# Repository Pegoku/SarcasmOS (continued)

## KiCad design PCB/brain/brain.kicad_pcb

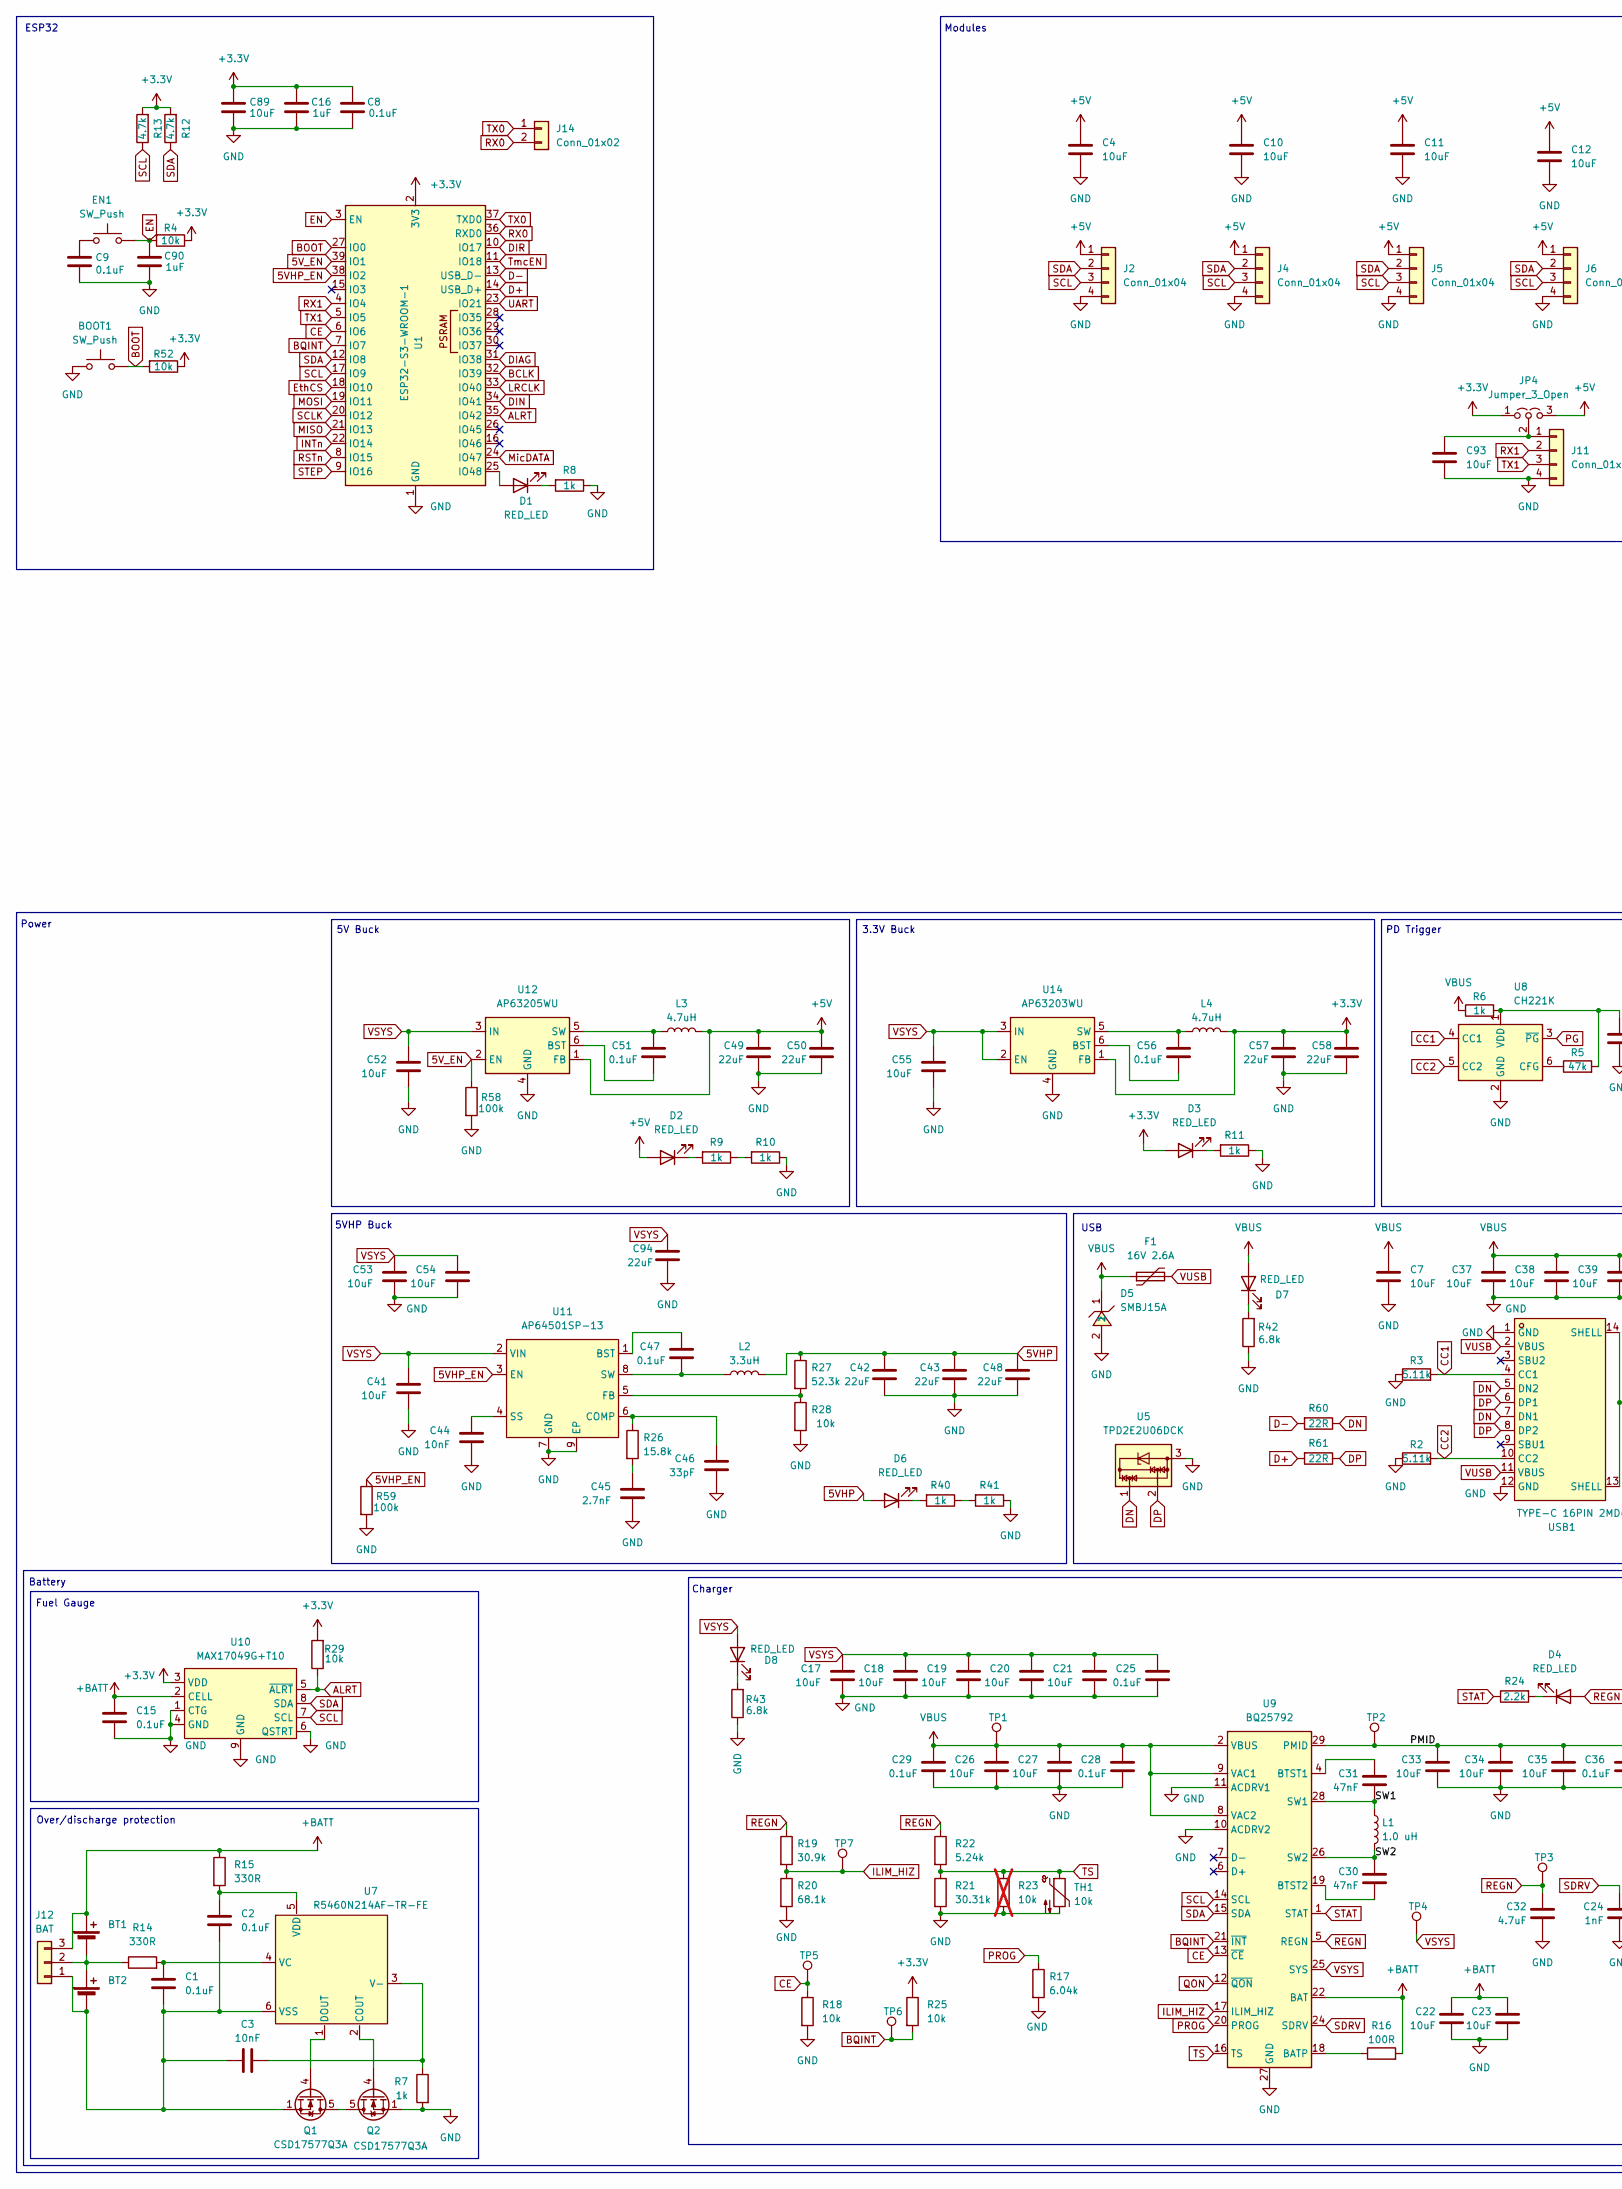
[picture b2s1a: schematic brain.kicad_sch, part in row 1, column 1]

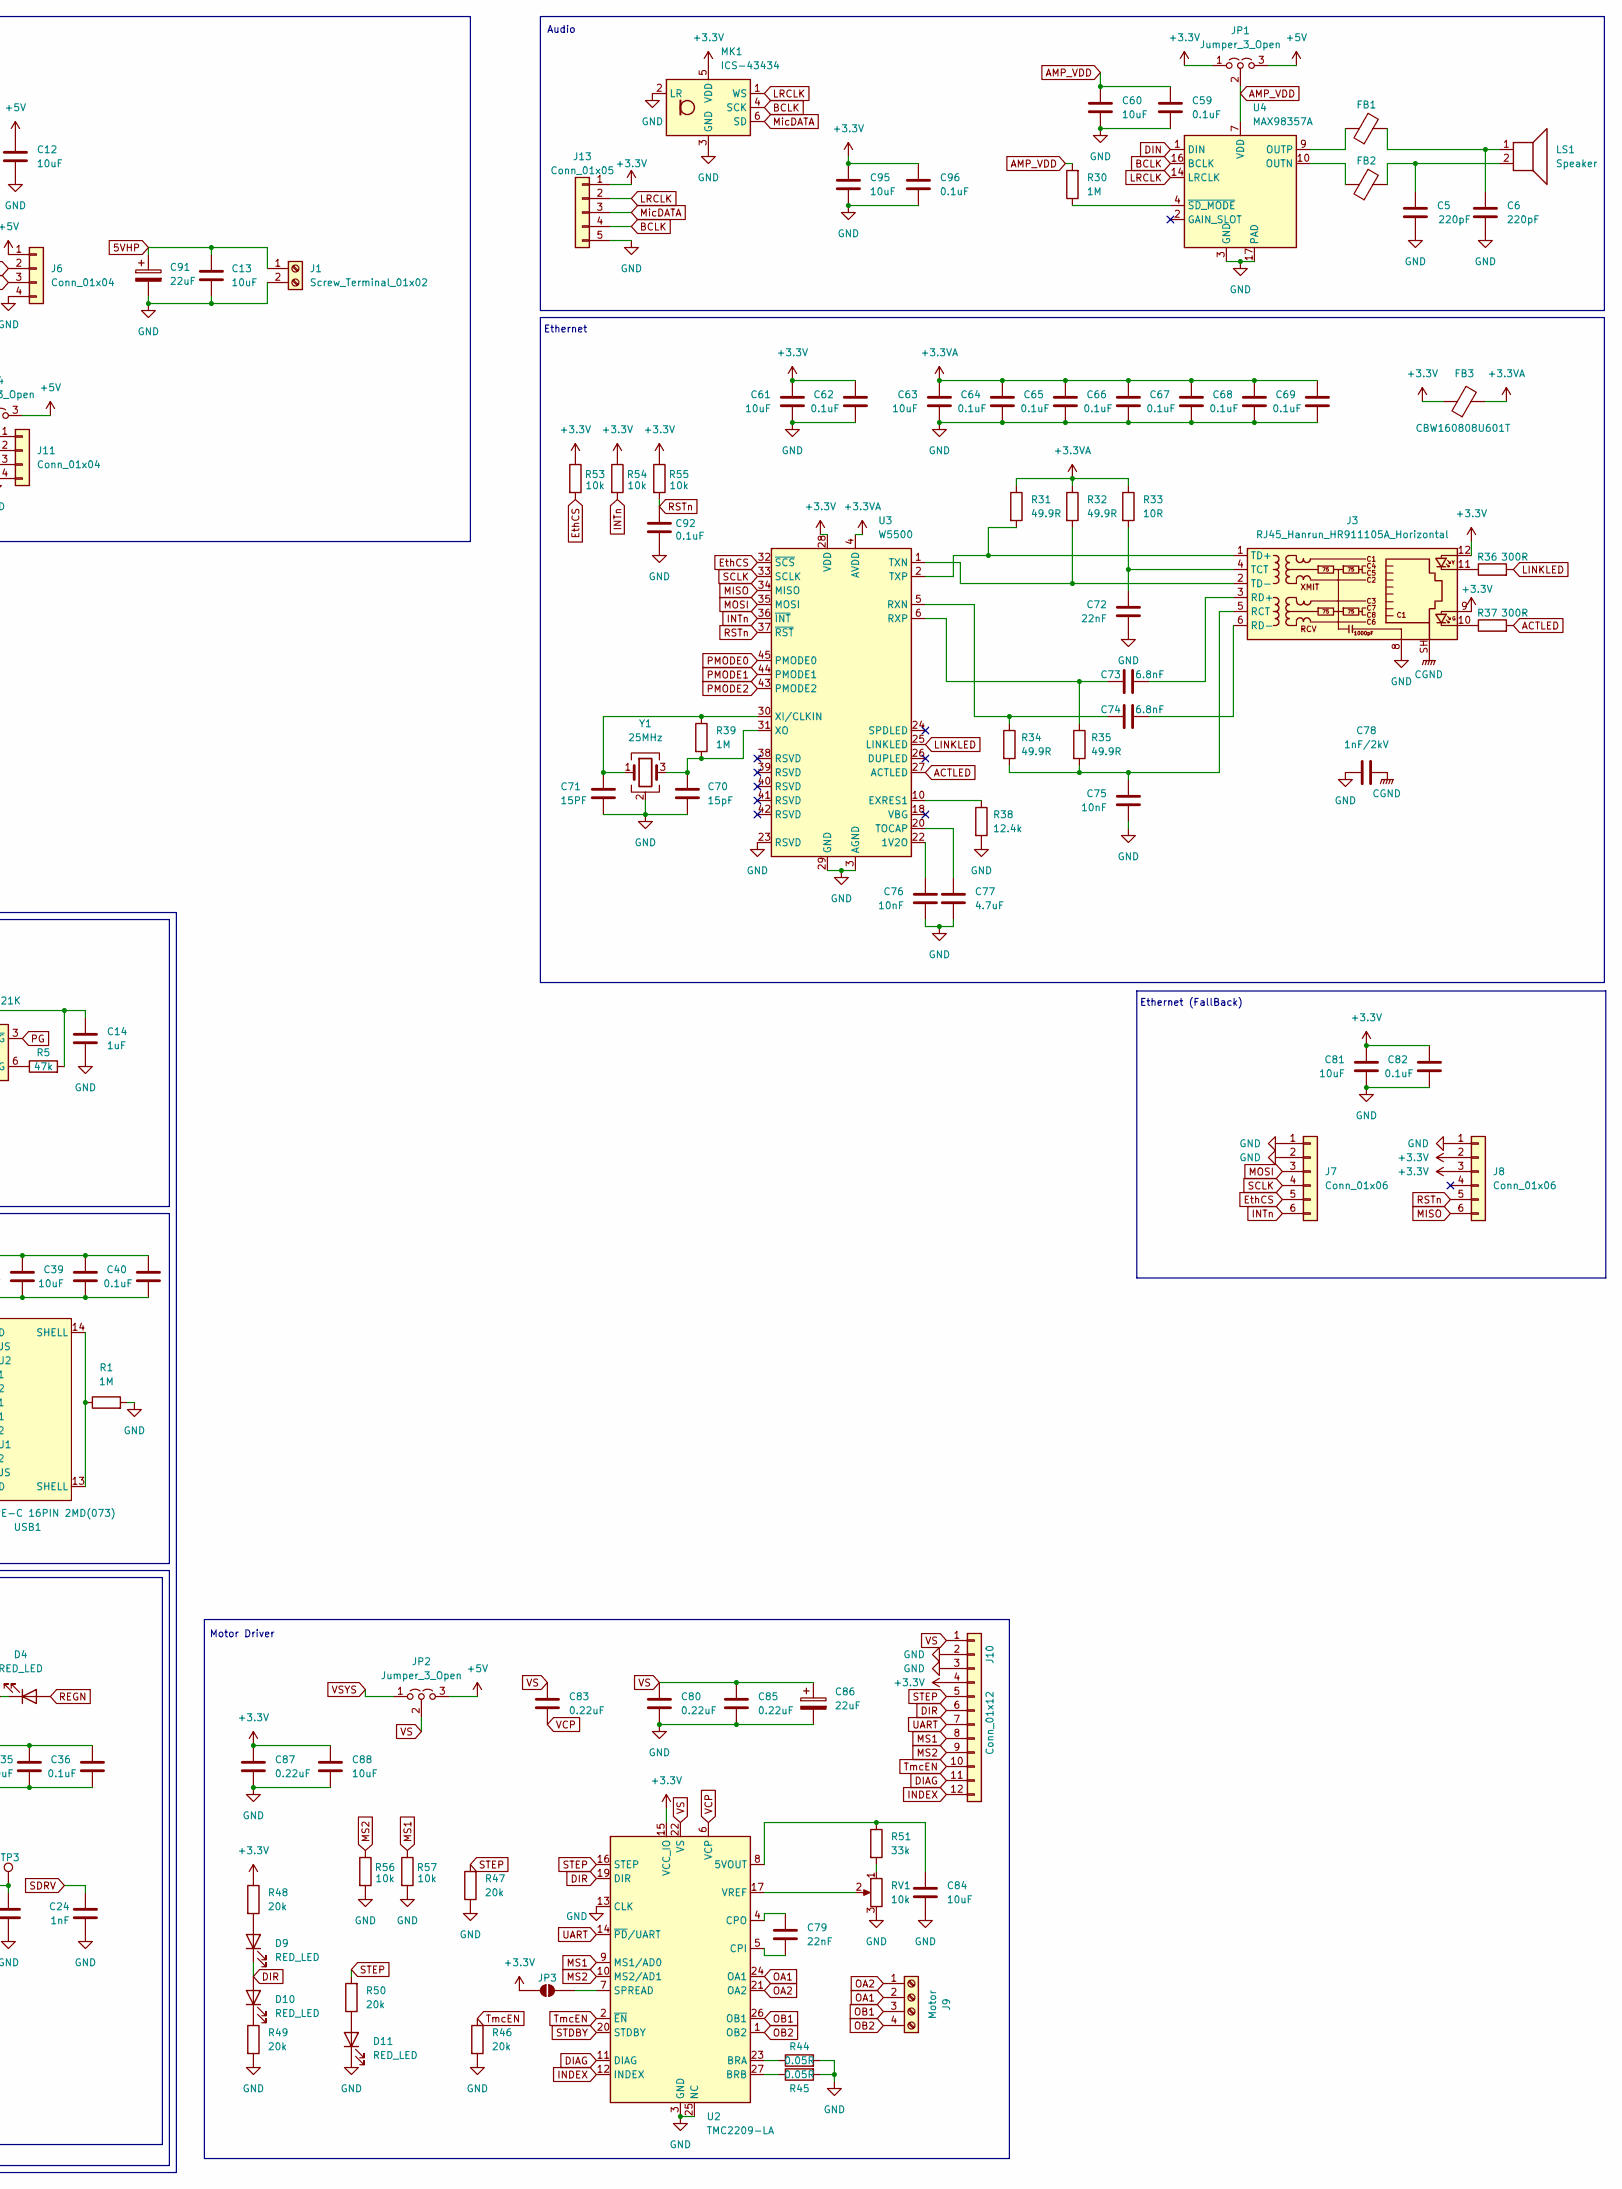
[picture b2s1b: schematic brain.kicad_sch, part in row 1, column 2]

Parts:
BOOT1: SW_Push; SW_SPST_TS-1088-xR025; LCSC Part C720477
BT1, BT2: Battery_Cell; PinHeader_1x02_P2.54mm_Vertical
C1, C2, C15, C29, C47, C51, C56, C92: 0.1uF; C_0603_1608Metric
C3, C44, C75, C76: 10nF; C_0603_1608Metric
C4, C7, C10, C11, C12, C13, C60, C61, C63, C81, C84, C88, C89, C93, C95: 10uF; C_0603_1608Metric
C5, C6: 220pF; C_0603_1608Metric
C8, C25, C28, C36, C40, C59, C62, C64, C65, C66, C67, C68, C69, C96: 0.1uF; C_0402_1005Metric; LCSC Part C77020
C9, C82: 0.1uF; C_0402_1005Metric
C14, C16, C90: 1uF; C_0603_1608Metric
C17, C18, C19, C20, C21, C22, C23, C26, C27, C33, C34, C35, C37, C38, C39, C41, C52, C53, C54, C55: 10uF; C_0603_1608Metric; LCSC Part C194427
C24: 1nF; C_0603_1608Metric
C30, C31: 47nF; C_0603_1608Metric
C32, C77: 4.7uF; C_0603_1608Metric
C42, C94: 22uF; C_0805_2012Metric; LCSC Part C162295
C43, C48, C49, C50, C57, C58: 22uF; C_0805_2012Metric
C45: 2.7nF; C_0603_1608Metric
C46: 33pF; C_0603_1608Metric
C70: 15pF; C_0603_1608Metric; LCSC Part C1644
C71: 15PF; C_0603_1608Metric; LCSC Part C1644
C72, C79: 22nF; C_0603_1608Metric
C73, C74: 6.8nF; C_0603_1608Metric
C78: 1nF/2kV; C_1206_3216Metric; LCSC Part C23631
C80, C83, C85, C87: 0.22uF; C_0603_1608Metric
C86, C91: 22uF; CAP-SMD_BD6.3-L6.6-W6.6-FD; LCSC Part C72505
D1, D2, D3, D4, D6, D7, D8, D9, D10, D11: RED_LED; LED_0603_1608Metric; LCSC Part C19171390
D5: SMBJ15A; SMB_L4.6-W3.6-LS5.3-RD; MPN SMBJ15A; LCSC Part C83846
EN1: SW_Push; SW_SPST_TS-1088-xR025; LCSC Part C720477
F1: 16V 2.6A; Fuse_1812_4532Metric_Pad1.30x3.40mm_HandSolder; LCSC Part C438899
FB1, FB2: FerriteBead; L_0603_1608Metric; LCSC Part C88989
FB3: CBW160808U601T; L_0603_1608Metric; LCSC Part C139183
J1: Screw_Terminal_01x02; TerminalBlock_Phoenix_PT-1,5-2-5.0-H_1x02_P5.00mm_Horizontal; LCSC Part C474881
J2, J4, J5, J6, J11: Conn_01x04; JST_XH_B4B-XH-A_1x04_P2.50mm_Vertical; LCSC Part C144395
J3: RJ45_Hanrun_HR911105A_Horizontal; LCSC Part C12074
J7, J8: Conn_01x06; PinSocket_1x06_P2.54mm_Vertical
J9: Motor; CONN-TH_4P-P2.54_MX128-2.54-GN01-04P-CU-Y-A; LCSC Part C5188444
J10: Conn_01x12; PinHeader_2x06_P2.54mm_Vertical
J12: BAT; JST_XH_B3B-XH-A_1x03_P2.50mm_Vertical
J13: Conn_01x05; JST_XH_B5B-XH-A_1x05_P2.50mm_Vertical
J14: Conn_01x02; PinSocket_1x02_P2.54mm_Vertical
JP1, JP2, JP4: Jumper_3_Open; PinHeader_1x03_P2.54mm_Vertical
JP3: SolderJumper_2_Open; SolderJumper-2_P1.3mm_Open_TrianglePad1.0x1.5mm
L1: 1.0 uH; IND-SMD_L7.1-W6.5-P5.60; LCSC Part C87572
L2: 3.3uH; IND-SMD_L11.5-W10.0_SMMS1040; LCSC Part C149592
L3, L4: 4.7uH; IND-SMD_L5.0-W5.0; LCSC Part C354606
LS1: Speaker; JST_XH_B2B-XH-AM_1x02_P2.50mm_Vertical
MK1: ICS-43434; InvenSense_ICS-43434-6_3.5x2.65mm
Q1, Q2: CSD17577Q3A; VSON-8_3.3x3.3mm_P0.65mm_NexFET
R1, R30, R39: 1M; R_0603_1608Metric
R2, R3: 5.11k; R_0603_1608Metric
R4, R18, R25, R28, R29, R52, R53, R54, R55, R56, R57: 10k; R_0603_1608Metric
R5: 47k; R_0603_1608Metric
R6, R7, R8, R9, R10, R11, R40, R41: 1k; R_0603_1608Metric
R12, R13: 4.7k; R_0603_1608Metric
R14, R15: 330R; R_0603_1608Metric
R16: 100R; R_0603_1608Metric
R17: 6.04k; R_0603_1608Metric
R19: 30.9k; R_0603_1608Metric
R20: 68.1k; R_0603_1608Metric
R21: 30.31k; R_0603_1608Metric
R22: 5.24k; R_0603_1608Metric
R23: 10k; R_0603_1608Metric; not fitted
R24: 2.2k; R_0603_1608Metric
R26: 15.8k; R_0603_1608Metric
R27: 52.3k; R_0603_1608Metric
R31, R32, R34, R35: 49.9R; R_0603_1608Metric
R33: 10R; R_0603_1608Metric
R36, R37: 300R; R_0603_1608Metric
R38: 12.4k; R_0603_1608Metric
R42, R43: 6.8k; R_0603_1608Metric
R44, R45: 0.05R; R_1206_3216Metric
R46, R47, R48, R49, R50: 20k; R_0603_1608Metric
R51: 33k; R_0603_1608Metric
R58, R59: 100k; R_0603_1608Metric
R60, R61: 22R; C_0402_1005Metric
RV1: 10k; RES-ADJ-SMD_3P-L3.8-W3.7_VGF39NCHXT; LCSC Part C22461454
TH1: 10k; PinHeader_1x02_P2.54mm_Vertical
TP1, TP2, TP3, TP4, TP5, TP6, TP7: TestPoint; TestPoint_Pad_D1.5mm
U1: ESP32-S3-WROOM-1; ESP32-S3-WROOM-1U; LCSC Part C2913199
U2: TMC2209-LA; VQFN-28-1EP_5x5mm_P0.5mm_EP3.7x3.7mm_ThermalVias
U3: W5500; LQFP-48_7x7mm_P0.5mm; LCSC Part C32843
U4: MAX98357A; TQFN-16-1EP_3x3mm_P0.5mm_EP1.23x1.23mm
U5: TPD2E2U06DCK; SOT-323_SC-70
U7: R5460N214AF-TR-FE; SOT-23-6_L2.9-W1.6-P0.95-LS2.8-BL; MPN R5460N214AF-TR-FE; LCSC Part C259719
U8: CH221K; SOT-23-6
U9: BQ25792; Texas_RQM0029A_VQFN-29_4x4mm_P0.4mm
U10: MAX17049G+T10; WSON-8_L2.0-W2.0-P0.50-BL-EP0.9; MPN MAX17049G+T10; LCSC Part C18185545
U11: AP64501SP-13; SOIC-8-1EP_3.9x4.9mm_P1.27mm_EP2.29x3mm_ThermalVias; MPN AP64501SP-13; LCSC Part C2071517
U12: AP63205WU; TSOT-23-6
U14: AP63203WU; TSOT-23-6
USB1: TYPE-C 16PIN 2MD(073); USB-C-SMD_TYPE-C-6PIN-2MD-073; LCSC Part C2765186
Y1: 25MHz; Crystal_SMD_3225-4Pin_3.2x2.5mm; LCSC Part C13740

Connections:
5VHP: C13.2, C42.2, C43.2, C48.2, C91.1, D6.2 (A), J1.1, L2.2, R27.1
5VHP_EN: R59.1, U1.38 (IO2), U11.3 (EN)
5V_EN: R58.1, U1.39 (IO1), U12.2 (EN)
+3.3V: C8.2, C16.2, C57.2, C58.2, C61.2, C62.2, C81.2, C82.2, C87.1, C88.2, C89.2, C95.1, C96.1, D3.2 (A), FB3.1, J3.9, J3.12, J8.2, J8.3, J10.4, J13.1, JP1.1 (A), JP3.1 (A), JP4.1 (A), L4.2, MK1.5 (VDD), R4.1, R12.2, R13.2, R25.1, R29.2, R48.1, R52.1, R53.1, R54.1, R55.1, U1.2 (3V3), U2.15 (VCC_IO), U3.28 (VDD), U10.3 (VDD), U14.1 (FB)
+3.3VA: C63.2, C64.2, C65.2, C66.2, C67.2, C68.2, C69.2, FB3.2, R31.1, R32.1, R33.1, U3.4 (AVDD), U3.8 (AVDD), U3.11 (AVDD), U3.15 (AVDD), U3.17 (AVDD), U3.21 (AVDD)
+5V: C4.2, C10.2, C11.2, C12.2, C49.2, C50.2, D2.2 (A), J2.1, J4.1, J5.1, J6.1, JP1.3 (B), JP2.3 (B), JP4.3 (B), L3.2, U12.1 (FB)
+BATT: BT1.1 (+), C15.1, C22.2, C23.2, J12.3, R15.1, R16.2, U9.22 (BAT), U9.23 (BAT), U10.2 (CELL)
/PMID: C33.2, C34.2, C35.2, C36.2, TP2.1 (1_1), U9.29 (PMID)
/SW1: C31.1, L1.1, U9.28 (SW1)
/SW2: C30.2, L1.2, U9.26 (SW2)
ACTLED: R37.2, U3.27 (ACTLED)
ALRT: R29.1, U1.35 (IO42), U10.5 (~ALRT)
AMP_VDD: C59.1, C60.1, JP1.2 (C), R30.2, U4.7 (VDD), U4.8 (VDD)
BCLK: J13.4, MK1.4 (SCK), U1.32 (IO39), U4.16 (BCLK)
BOOT: BOOT1.2, R52.2, U1.27 (IO0)
BQINT: R25.2, TP6.1 (1_1), U1.7 (IO7), U9.21 (~INT)
CC1: R3.2, U8.4 (CC1), USB1.4 (CC1)
CC2: R2.2, U8.5 (CC2), USB1.10 (CC2)
CE: R18.1, TP5.1 (1_1), U1.6 (IO6), U9.13 (~CE)
CGND: C78.2, J3.SH
D+: R61.2, U1.14 (USB_D+)
D-: R60.2, U1.13 (USB_D-)
DIAG: J10.11, U1.31 (IO38), U2.11 (DIAG)
DIN: U1.34 (IO41), U4.1 (DIN)
DIR: D9.1 (K), D10.2 (A), J10.6, U1.10 (IO17), U2.19 (DIR)
DN: R60.1, U5.1, USB1.5 (DN2), USB1.7 (DN1)
DP: R61.1, U5.2, USB1.6 (DP1), USB1.8 (DP2)
EN: C90.2, EN1.2, R4.2, U1.3 (EN)
EthCS: J7.5, R53.2, U1.18 (IO10), U3.32 (~SCS)
GND: BOOT1.1, C4.1, C5.2, C6.2, C7.1, C8.1, C9.1, C10.1, C11.1, C12.1, C13.1, C14.1, C15.2, C16.1, C17.1, C18.1, C19.1, C20.1, C21.1, C22.1, C23.1, C24.1, C25.1, C26.1, C27.1, C28.1, C29.1, C32.1, C33.1, C34.1, C35.1, C36.1, C37.1, C38.1, C39.1, C40.1, C41.1, C42.1, C43.1, C44.1, C45.1, C46.1, C48.1, C49.1, C50.1, C52.1, C53.1, C54.1, C55.1, C57.1, C58.1, C59.2, C60.2, C61.1, C62.1, C63.1, C64.1, C65.1, C66.1, C67.1, C68.1, C69.1, C70.2, C71.2, C72.1, C75.1, C76.1, C77.1, C78.1, C80.2, C81.1, C82.1, C84.1, C85.2, C86.2, C87.2, C88.1, C89.1, C90.1, C91.2, C92.1, C93.1, C94.1, C95.2, C96.2, D5.2, D11.1 (K), J1.2, J2.4, J3.8, J4.4, J5.4, J6.4, J7.1, J7.2, J8.1, J10.2, J10.3, J11.4, J13.5, MK1.2 (LR), MK1.3 (GND), Q2.1 (S), Q2.2 (S), Q2.3 (S), R1.2, R2.1, R3.1, R7.2, R8.1, R10.1, R11.1, R17.2, R18.2, R20.2, R21.2, R23.2, R28.2, R38.2, R41.1, R42.1, R43.1, R44.2, R45.2, R46.2, R47.1, R49.2, R56.2, R57.2, R58.2, R59.2, RV1.3, TH1.2, U1.1 (GND), U1.40 (GND), U1.41 (GND), U2.3 (GND), U2.13 (CLK), U2.18 (GND), U2.25 (NC), U2.29 (GND), U3.3 (AGND), U3.9 (AGND), U3.14 (AGND), U3.16 (AGND), U3.19 (AGND), U3.23 (RSVD), U3.29 (GND), U3.48 (AGND), U4.3 (GND), U4.11 (GND), U4.15 (GND), U4.17 (PAD), U5.3, U8.2 (GND), U9.10 (ACDRV2), U9.11 (ACDRV1), U9.27 (GND), U10.1 (CTG), U10.4 (GND), U10.6 (QSTRT), U10.9 (GND), U11.7 (GND), U11.9 (EP), U12.4 (GND), U14.4 (GND), USB1.1 (GND), USB1.12 (GND), Y1.2 (G), Y1.4 (G)
ILIM_HIZ: R19.2, R20.1, TP7.1 (1_1), U9.17 (ILIM_HIZ)
INDEX: J10.12, U2.12 (INDEX)
INTn: J7.6, R54.2, U1.22 (IO14), U3.36 (~INT)
LINKLED: R36.2, U3.25 (LINKLED)
LRCLK: J13.2, MK1.1 (WS), U1.33 (IO40), U4.14 (LRCLK)
MISO: J8.6, U1.21 (IO13), U3.34 (MISO)
MOSI: J7.3, U1.19 (IO11), U3.35 (MOSI)
MS1: J10.8, R57.1, U2.9 (MS1/AD0)
MS2: J10.9, R56.1, U2.10 (MS2/AD1)
MicDATA: J13.3, MK1.6 (SD), U1.24 (IO47)
unnamed: BT1.2 (-), BT2.1 (+), J12.2, R14.1
unnamed: BT2.2 (-), C1.2, C2.2, C3.1, J12.1, Q1.1 (S), Q1.2 (S), Q1.3 (S), U7.6 (VSS)
unnamed: C5.1, FB2.2, LS1.2
unnamed: C6.1, FB1.2, LS1.1
unnamed: C9.2, EN1.1
unnamed: C45.2, R26.2
unnamed: D1.2 (A), U1.25 (IO48)
unnamed: D1.1 (K), R8.2
unnamed: D2.1 (K), R9.2
unnamed: D3.1 (K), R11.2
unnamed: D4.1 (K), R24.2
unnamed: D6.1 (K), R40.2
unnamed: D7.1 (K), R42.2
unnamed: D8.1 (K), R43.2
unnamed: D9.2 (A), R48.2
unnamed: D10.1 (K), R49.1
unnamed: D11.2 (A), R50.1
unnamed: J3.10, R37.1
unnamed: J3.11, R36.1
unnamed: C75.2, J3.5 (RCT), R34.2, R35.2
unnamed: C73.1, J3.3 (RD+)
unnamed: C74.1, J3.6 (RD-)
unnamed: C72.2, J3.4 (TCT), R33.2
unnamed: J3.1 (TD+), R31.2, U3.2 (TXP)
unnamed: J3.2 (TD-), R32.2, U3.1 (TXN)
unnamed: C93.2, J11.1, JP4.2 (C)
unnamed: JP3.2 (B), U2.7 (SPREAD)
unnamed: Q1.5 (D), Q2.5 (D)
unnamed: Q1.4 (G), U7.1 (DOUT)
unnamed: Q2.4 (G), U7.2 (COUT)
unnamed: R1.1, USB1.13 (SHELL), USB1.14 (SHELL)
unnamed: R9.1, R10.2
unnamed: R40.1, R41.2
unnamed: R51.2, RV1.1
unnamed: C84.2, R51.1, U2.8 (5VOUT)
unnamed: R44.1, U2.23 (BRA)
unnamed: R45.1, U2.27 (BRB)
unnamed: C79.2, U2.5 (CPI)
unnamed: C79.1, U2.4 (CPO)
unnamed: RV1.2, U2.17 (VREF)
unnamed: C76.2, U3.22 (1V2O)
unnamed: R38.1, U3.10 (EXRES1)
unnamed: C74.2, R34.1, U3.5 (RXN)
unnamed: C73.2, R35.1, U3.6 (RXP)
unnamed: C77.2, U3.20 (TOCAP)
unnamed: C71.1, R39.1, U3.30 (XI/CLKIN), Y1.1
unnamed: C70.1, R39.2, U3.31 (XO), Y1.3
unnamed: FB2.1, U4.10 (OUTN)
unnamed: FB1.1, U4.9 (OUTP)
unnamed: R30.1, U4.4 (~SD_MODE)
unnamed: C3.2, R7.1, U7.3 (V-)
unnamed: C1.1, R14.2, U7.4 (VC)
unnamed: C2.1, R15.2, U7.5 (VDD)
unnamed: R5.1, U8.6 (CFG)
unnamed: C14.2, R5.2, R6.2, U8.1 (VDD)
unnamed: R16.1, U9.18 (BATP)
unnamed: C31.2, U9.4 (BTST1)
unnamed: C30.1, U9.19 (BTST2)
unnamed: C47.2, U11.1 (BST)
unnamed: C46.2, R26.1, U11.6 (COMP)
unnamed: R27.2, R28.1, U11.5 (FB)
unnamed: C44.2, U11.4 (SS)
unnamed: C47.1, L2.1, U11.8 (SW)
unnamed: C51.1, U12.6 (BST)
unnamed: C51.2, L3.1, U12.5 (SW)
unnamed: C56.1, U14.6 (BST)
unnamed: C56.2, L4.1, U14.5 (SW)
OA1: J9.2, U2.24 (OA1)
OA2: J9.1, U2.21 (OA2)
OB1: J9.3, U2.26 (OB1)
OB2: J9.4, U2.1 (OB2)
PG: U8.3 (~PG)
PMODE0: U3.45 (PMODE0)
PMODE1: U3.44 (PMODE1)
PMODE2: U3.43 (PMODE2)
PROG: R17.1, U9.20 (PROG)
QON: U9.12 (~QON)
REGN: C32.2, D4.2 (A), R19.1, R22.1, TP3.1 (1_1), U9.5 (REGN)
RSTn: C92.2, J8.5, R55.2, U1.8 (IO15), U3.37 (~RST)
RX0: J14.2, U1.36 (RXD0)
RX1: J11.2, U1.4 (IO4)
SCL: J2.3, J4.3, J5.3, J6.3, R13.1, U1.17 (IO9), U9.14 (SCL), U10.7 (SCL)
SCLK: J7.4, U1.20 (IO12), U3.33 (SCLK)
SDA: J2.2, J4.2, J5.2, J6.2, R12.1, U1.12 (IO8), U9.15 (SDA), U10.8 (SDA)
SDRV: C24.2, U9.24 (SDRV)
STAT: R24.1, U9.1 (STAT)
STDBY: U2.20 (STDBY)
STEP: J10.5, R47.2, R50.2, U1.9 (IO16), U2.16 (STEP)
TS: R21.1, R22.2, R23.1, TH1.1, U9.16 (TS)
TX0: J14.1, U1.37 (TXD0)
TX1: J11.3, U1.5 (IO5)
TmcEN: J10.10, R46.1, U1.11 (IO18), U2.2 (~EN)
UART: J10.7, U1.23 (IO21), U2.14 (~PD/UART)
VBUS: C7.2, C26.2, C27.2, C28.2, C29.2, C37.2, C38.2, C39.2, C40.2, D5.1, D7.2 (A), F1.1, R6.1, TP1.1 (1_1), U9.2 (VBUS), U9.3 (VBUS), U9.8 (VAC2), U9.9 (VAC1)
VCP: C83.2, U2.6 (VCP)
VS: C80.1, C83.1, C85.1, C86.1, J10.1, JP2.2 (C), U2.22 (VS), U2.28 (VS)
VSYS: C17.2, C18.2, C19.2, C20.2, C21.2, C25.2, C41.2, C52.2, C53.2, C54.2, C55.2, C94.2, D8.2 (A), JP2.1 (A), TP4.1 (1_1), U9.25 (SYS), U11.2 (VIN), U12.3 (IN), U14.2 (EN), U14.3 (IN)
VUSB: F1.2, USB1.2 (VBUS), USB1.11 (VBUS)

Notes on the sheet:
ESP32
5VHP Buck
Over/discharge protection
Battery
3.3V Buck
Fuel Gauge
5V Buck
USB
Power
Motor Driver
Ethernet (FallBack)
Charger
Audio
Modules
PD Trigger
Ethernet

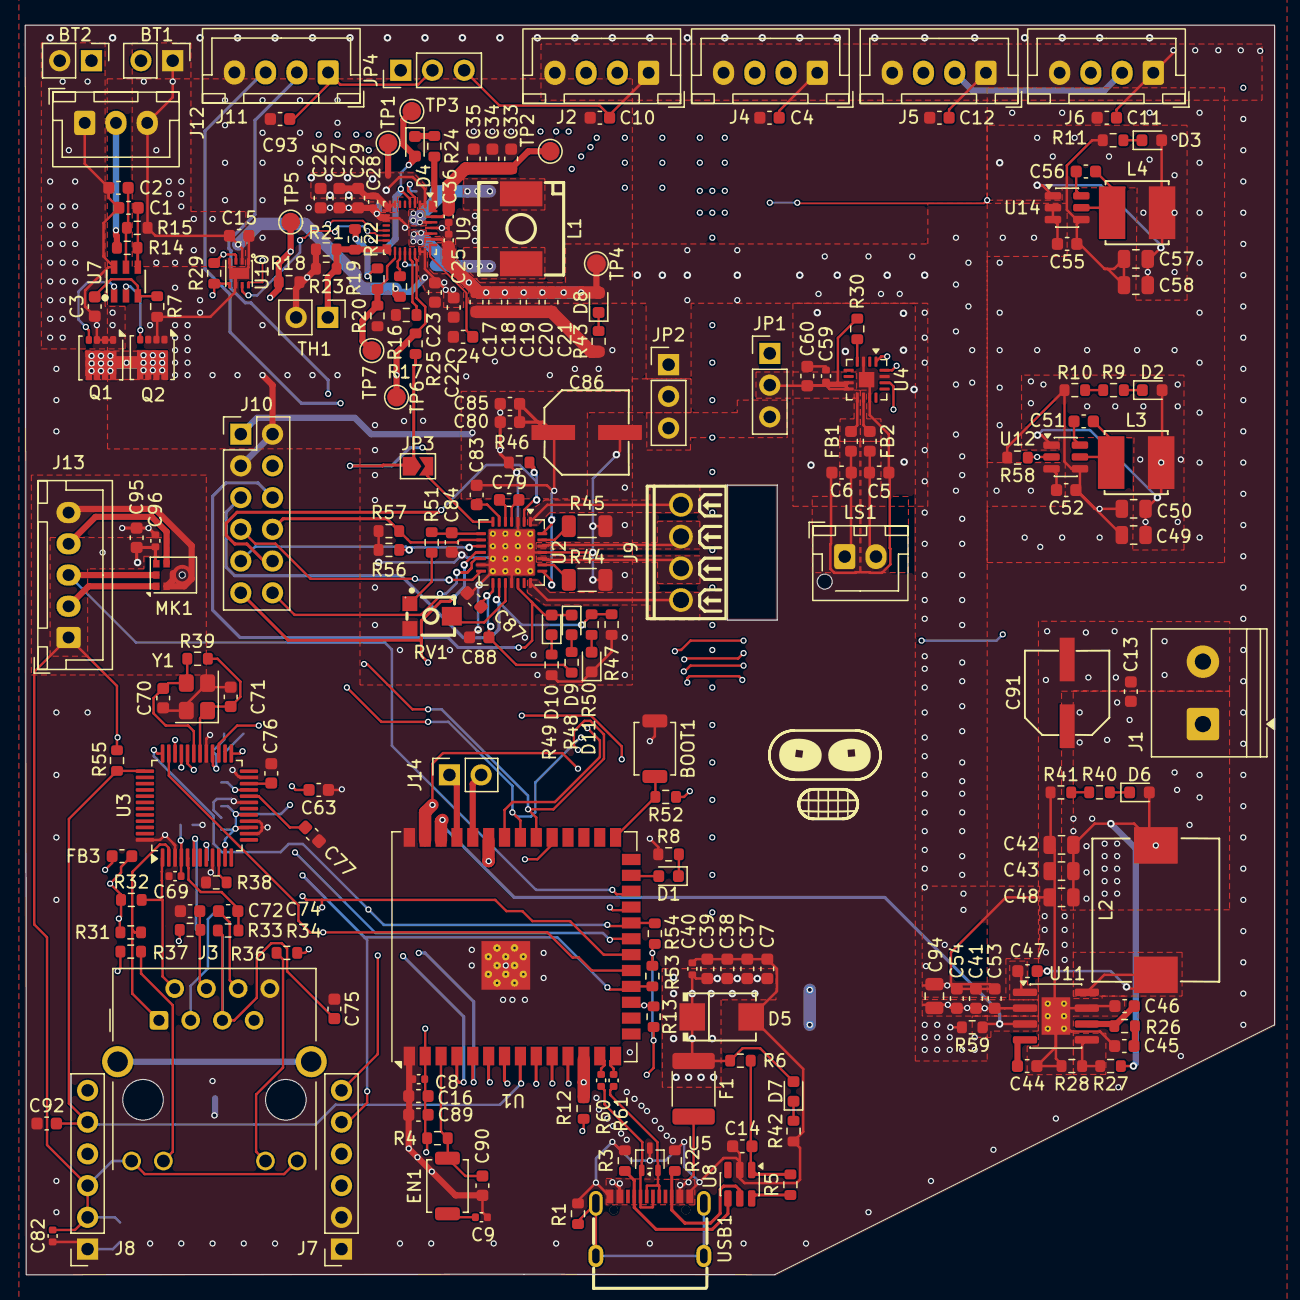
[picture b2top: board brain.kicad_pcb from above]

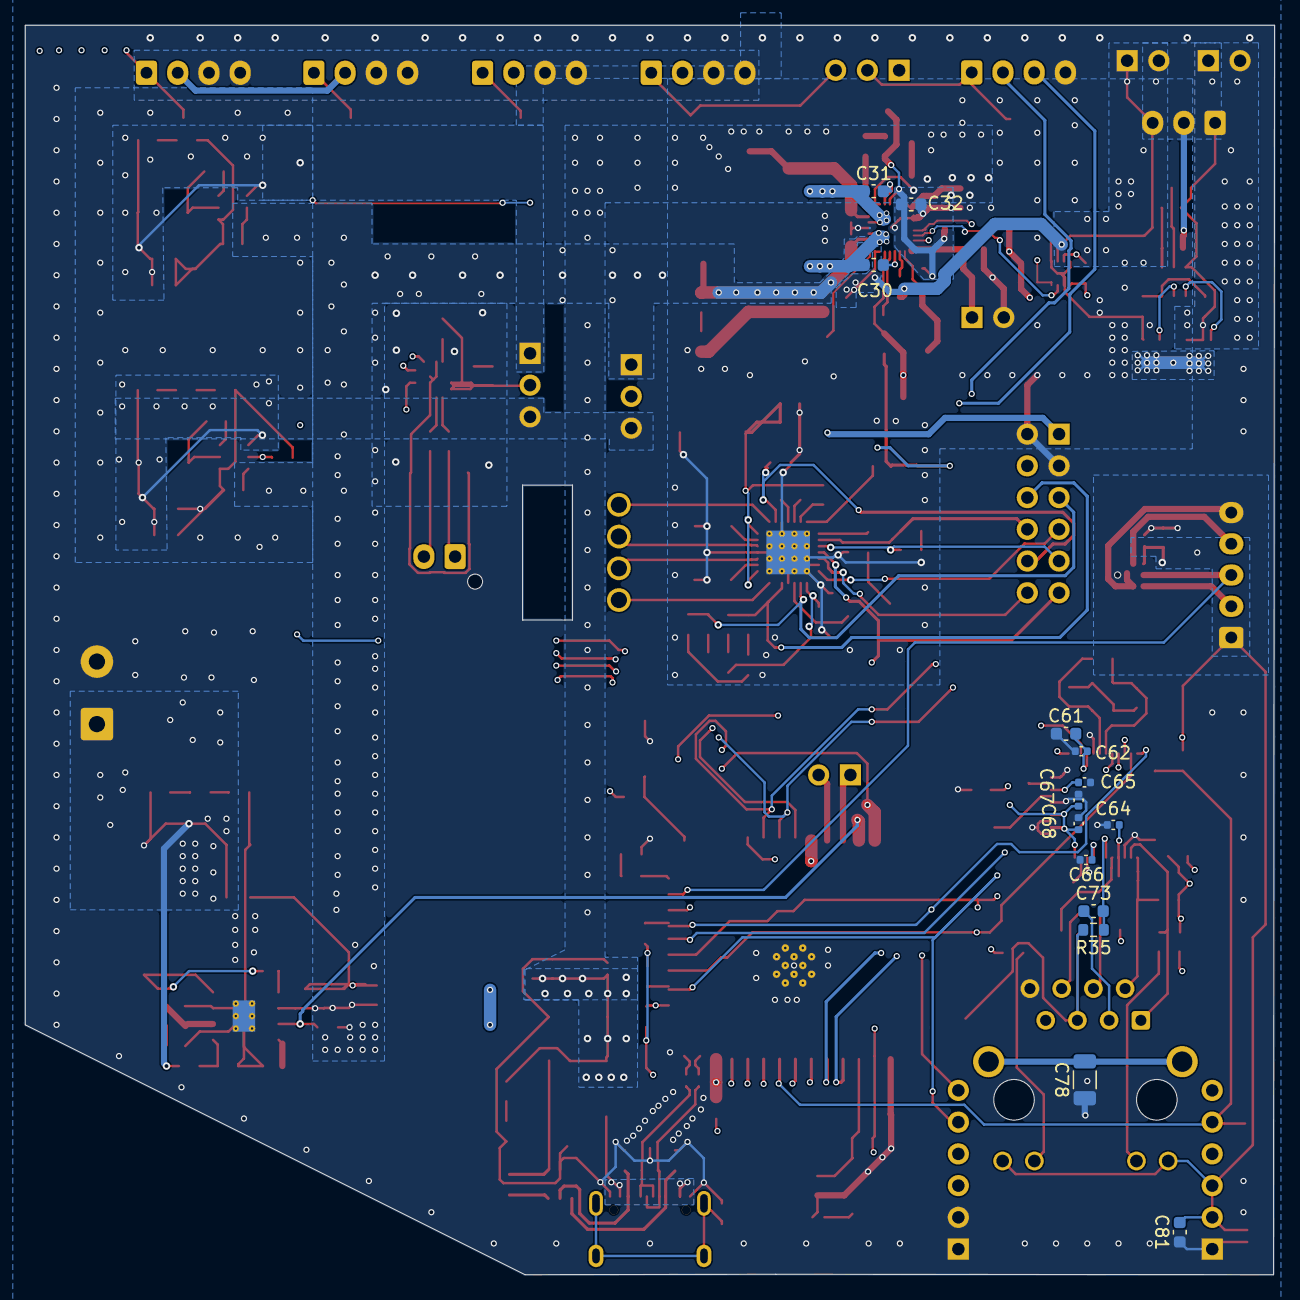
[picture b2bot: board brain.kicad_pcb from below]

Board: 4 copper layers, 100.0 x 100.0 mm, 225 parts (14 on the bottom side), 132 nets.

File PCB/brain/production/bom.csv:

Designator,Footprint,Quantity,Value,LCSC Part #
"BOOT1, EN1",SW_SPST_TS-1088-xR025,2,SW_Push,C720477
"BT1, BT2",PinHeader_1x02_P2.54mm_Vertical,2,Battery_Cell,
"C1, C15, C2, C29, C47, C51, C56, C92",0603,8,0.1uF,
"C10, C11, C12, C13, C4, C60, C61, C63, C7, C81, C84, C88, C89, C93, C95",0603,15,10uF,
"C14, C16, C90",0603,3,1uF,
"C17, C18, C19, C20, C21, C22, C23, C26, C27, C33, C34, C35, C37, C38, C39, C41, C52, C53, C54, C55",0603,20,10uF,C194427
C24,0603,1,1nF,
"C25, C28, C36, C40, C59, C62, C64, C65, C66, C67, C68, C69, C8, C96",0402,14,0.1uF,C77020
"C3, C44, C75, C76",0603,4,10nF,
"C30, C31",0603,2,47nF,
"C32, C77",0603,2,4.7uF,
"C42, C94",0805,2,22uF,C162295
"C43, C48, C49, C50, C57, C58",0805,6,22uF,
C45,0603,1,2.7nF,
C46,0603,1,33pF,
"C5, C6",0603,2,220pF,
"C70, C71",0603,2,15pF,C1644
"C72, C79",0603,2,22nF,
"C73, C74",0603,2,6.8nF,
C78,1206,1,1nF/2kV,C23631
"C80, C83, C85, C87",0603,4,0.22uF,
"C82, C9",0402,2,0.1uF,
"C86, C91",CAP-SMD_BD6.3-L6.6-W6.6-FD,2,22uF,C72505
"D1, D10, D11, D2, D3, D4, D6, D7, D8, D9",0603,10,RED_LED,C19171390
D5,SMB_L4.6-W3.6-LS5.3-RD,1,SMBJ15A,C83846
F1,1812,1,16V 2.6A,C438899
"FB1, FB2",0603,2,FerriteBead,C88989
FB3,0603,1,CBW160808U601T,C139183
J1,"TerminalBlock_Phoenix_PT-1,5-2-5.0-H_1x02_P5.00mm_Horizontal",1,Screw_Terminal_01x02,C474881
J10,PinHeader_2x06_P2.54mm_Vertical,1,Conn_01x12,
"J11, J2, J4, J5, J6",JST_XH_B4B-XH-A_1x04_P2.50mm_Vertical,5,Conn_01x04,C144395
J12,JST_XH_B3B-XH-A_1x03_P2.50mm_Vertical,1,BAT,
J13,JST_XH_B5B-XH-A_1x05_P2.50mm_Vertical,1,Conn_01x05,
J14,PinSocket_1x02_P2.54mm_Vertical,1,Conn_01x02,
J3,RJ45_Hanrun_HR911105A_Horizontal,1,RJ45_Hanrun_HR911105A_Horizontal,C12074
"J7, J8",PinSocket_1x06_P2.54mm_Vertical,2,Conn_01x06,
J9,CONN-TH_4P-P2.54_MX128-2.54-GN01-04P-CU-Y-A,1,Motor,C5188444
L1,IND-SMD_L7.1-W6.5-P5.60,1,1.0 uH,C87572
L2,IND-SMD_L11.5-W10.0_SMMS1040,1,3.3uH,C149592
"L3, L4",IND-SMD_L5.0-W5.0,2,4.7uH,C354606
LS1,JST_XH_B2B-XH-AM_1x02_P2.50mm_Vertical,1,Speaker,
MK1,InvenSense_ICS-43434-6_3.5x2.65mm,1,ICS-43434,
"Q1, Q2",VSON-8_3.3x3.3mm_P0.65mm_NexFET,2,CSD17577Q3A,
"R1, R30, R39",0603,3,1M,
"R10, R11, R40, R41, R6, R7, R8, R9",0603,8,1k,
"R12, R13",0603,2,4.7k,
"R14, R15",0603,2,330R,
R16,0603,1,100R,
R17,0603,1,6.04k,
"R18, R23, R25, R28, R29, R4, R52, R53, R54, R55, R56, R57",0603,12,10k,
R19,0603,1,30.9k,
"R2, R3",0603,2,5.11k,
R20,0603,1,68.1k,
R21,0603,1,30.31k,
R22,0603,1,5.24k,
R24,0603,1,2.2k,
R26,0603,1,15.8k,
R27,0603,1,52.3k,
"R31, R32, R34, R35",0603,4,49.9R,
R33,0603,1,10R,
"R36, R37",0603,2,300R,
R38,0603,1,12.4k,
"R42, R43",0603,2,6.8k,
"R44, R45",1206,2,0.05R,
"R46, R47, R48, R49, R50",0603,5,20k,
R5,0603,1,47k,
R51,0603,1,33k,
"R58, R59",0603,2,100k,
"R60, R61",0402,2,22R,
RV1,RES-ADJ-SMD_3P-L3.8-W3.7_VGF39NCHXT,1,10k,C22461454
TH1,PinHeader_1x02_P2.54mm_Vertical,1,10k,
"TP1, TP2, TP3, TP4, TP5, TP6, TP7",TestPoint_Pad_D1.5mm,7,TestPoint,
U1,ESP32-S3-WROOM-1U,1,ESP32-S3-WROOM-1,C2913199
U10,WSON-8_L2.0-W2.0-P0.50-BL-EP0.9,1,MAX17049G+T10,C18185545
U11,SOIC-8-1EP_3.9x4.9mm_P1.27mm_EP2.29x3mm_ThermalVias,1,AP64501SP-13,C2071517
U12,TSOT-23-6,1,AP63205WU,
U14,TSOT-23-6,1,AP63203WU,
U2,VQFN-28-1EP_5x5mm_P0.5mm_EP3.7x3.7mm_ThermalVias,1,TMC2209-LA,
U3,LQFP-48_7x7mm_P0.5mm,1,W5500,C32843
U4,TQFN-16-1EP_3x3mm_P0.5mm_EP1.23x1.23mm,1,MAX98357A,
U5,SOT-323_SC-70,1,TPD2E2U06DCK,
U7,SOT-23-6_L2.9-W1.6-P0.95-LS2.8-BL,1,R5460N214AF-TR-FE,C259719
U8,SOT-23-6,1,CH221K,
U9,Texas_RQM0029A_VQFN-29_4x4mm_P0.4mm,1,BQ25792,
USB1,USB-C-SMD_TYPE-C-6PIN-2MD-073,1,TYPE-C 16PIN 2MD(073),C2765186
Y1,Crystal_SMD_3225-4Pin_3.2x2.5mm,1,25MHz,C13740

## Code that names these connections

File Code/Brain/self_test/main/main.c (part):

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
    if (gpio_get_level(PIN_5V_EN) == 1) {
        print_result(RESULT_WARN, "+5V buck control",
                     "GPIO1 enable is high; output voltage has no feedback (measure +5V)");
    } else {
        print_result(RESULT_FAIL, "+5V buck control", "GPIO1 did not latch high");
    }

    if (gpio_get_level(PIN_5VHP_EN) == 1) {
        print_result(RESULT_WARN, "5VHP buck control",
                     "GPIO2 enable is high; output voltage has no feedback (measure 5VHP)");
    } else {
        print_result(RESULT_FAIL, "5VHP buck control", "GPIO2 did not latch high");
    }

    char detail[128];
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    }

    unsigned found = 0;
    printf("\nI2C scan on GPIO8/GPIO9 at %d Hz:\n", CONFIG_BRAIN_SELF_TEST_I2C_FREQ_HZ);
    for (uint8_t address = 0x08; address <= 0x77; ++address) {
        if (i2c_present(address)) {
            printf("  - 0x%02X: %s\n", address, known_i2c_device(address));
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            I2S_DATA_BIT_WIDTH_32BIT, I2S_SLOT_MODE_STEREO),
        .gpio_cfg = {
            .mclk = I2S_GPIO_UNUSED,
            .bclk = PIN_I2S_BCLK,
            .ws = PIN_I2S_LRCLK,
            .dout = PIN_I2S_DOUT,
            .din = PIN_I2S_DIN,
            .invert_flags = { 0 },
        },
    };
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        printf("\n[FAIL] charger control: %s\n", esp_err_to_name(err));
        return;
    }
    printf("\n[OK] charger is %s (active-low CE GPIO6=%d).\n",
           enabled ? "enabled" : "disabled", enabled ? 0 : 1);
}

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    printf("  BQINT=%d  fuel ALRT=%d  W5500 INT=%d  TMC DIAG=%d\n",
           gpio_get_level(PIN_BQ_INT), gpio_get_level(PIN_FUEL_ALERT),
           gpio_get_level(PIN_ETH_INT), gpio_get_level(PIN_TMC_DIAG));
    printf("  TMC driver remains disabled (TmcEN=%d).\n", gpio_get_level(PIN_TMC_EN));
}

static void manual_wifi_scan(void)
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
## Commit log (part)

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2026-04-03 base
2026-04-04 visor
2026-04-04 head, wip
2026-04-05 bender-voz.json
2026-04-06 transcripts
2026-04-06 test.py
2026-04-06 clips!!
2026-04-06 checkAudioHz
2026-04-06 more clips
2026-04-06 upload
2026-04-06 This is the bass whith and without top lid
2026-04-07 classify audios
2026-04-08 organize folders
2026-04-08 transcribe
2026-04-08 dockerfile
2026-04-08 dockers
2026-04-13 Dockerfile.rocm64
2026-04-14 cudaTest
2026-04-14 testingAudios
2026-04-17 more audios
2026-04-17 finetuning test
2026-04-17 even mroe test outputs
2026-04-17 final audio gen
2026-04-17 gradeScriot
2026-04-18 audio grades base done
2026-04-18 audios
2026-04-19 very good audio
2026-04-19 using replicate API
2026-04-19 vclone-api.py
2026-04-19 stream api
2026-04-30 minimax test
2026-04-30 voice splitter
2026-04-30 copyright folder
2026-04-30 Pyannote
2026-04-30 environment configs
2026-05-04 replicate bender clone
2026-05-04 fix minimaxtts.py
2026-05-06 minimax scripts
2026-05-06 output tests
2026-05-06 Piannote test
2026-05-06 xtts
2026-05-06 improve vclone-api
2026-05-07 add streaming
2026-05-07 transcribe audios
2026-05-07 xttsTests
2026-05-07 sam script
2026-05-07 moar outputs
2026-05-07 Workflow folder
2026-05-08 ignore generated model artifacts
2026-05-08 tts scripts
2026-05-15 fix whisper
2026-05-15 aio workflow
2026-05-15 play after gen
2026-05-15 toolcalling for the AI, added get_weather, get_time, eye_look, set_expression, robot_status
2026-05-16 Start of the Eye PCB
2026-05-16 continue with rp2040
2026-05-17 finish schematic
2026-05-17 add buttons
2026-05-17 finish placement
2026-05-17 mostly routed
2026-05-18 bigger vias
2026-05-18 continue routing
2026-05-18 fix all DRC errors
2026-05-18 finish Eye PCB
2026-05-19 BOM + improvements
2026-05-20 Do web
2026-05-20 Change svg
2026-05-20 Refactor code structure for improved readability and maintainability
2026-05-20 mouth pcb
2026-05-20 web svg fix
2026-05-20 Add .venv to .gitignore to exclude virtual environment files
2026-05-20 Enhance face view functionality and styling for improved user experience
2026-05-20 try to do bender talks
2026-05-20 continue on mouth PCB
2026-05-21 I add animations for the loading audios
2026-05-21 I ad a chat bot and i resolve some errors
2026-05-21 start placing Mouth PCB components
2026-05-22 I add a new multiple chat fot the open voice chat
2026-05-22 I change the voice chat, to see a more astetic
2026-05-23 more pcb
2026-05-23 finish mouth pcb
2026-05-23 The chat now have remember
2026-05-23 I have improved the visual of the page
2026-05-23 I add api hecks
2026-05-23 logos
2026-05-24 eye pcb
2026-05-24 fix api base
2026-05-24 I change carpets
2026-05-24 login with google
2026-05-27 Page "Allways active"
2026-05-27 I do a new home page
2026-05-27 Admin panel, new better login and easteregg
2026-05-27 over/discharge prot + Fuel Gauge
2026-05-27 Multitasking mode
2026-05-29 translate all the page, and do a developer mode
2026-05-29 mostly do power part
2026-05-29 switch to minimax/speech-2.8-turbo
2026-05-29 buck HP done
2026-05-30 I do a creditrs sistem in the web
2026-05-31 ethernet
2026-06-01 audioGens
2026-06-01 PCB/brain/
2026-06-01 start working on esp32
2026-06-01 brain sch done
2026-06-02 add footprints to BrainPCB
2026-06-03 Add Konami easter egg functionality with audio and CSS choreography
    - Created README.md for asset placement instructions for the Konami Code audio.
    - Added konami-rickroll.css for the visual choreography of the easter egg.
    - Included konami.wav audio file for the easter egg activation.
    - Documented easter egg details in backend README.md.
    - Added support_requests.json for tracking user inquiries related to the easter egg.
    - Updated support assistant README.md with guidelines for user interaction and humor style.
2026-06-03 start pcb routing
2026-06-03 TMC2209 done
2026-06-03 Implement support chat functionality with new chat creation and selection
2026-06-04 Add user profile setup with form and storage functionality
2026-06-04 Add edit profile button and update stylesheets for profile editing
2026-06-04 more pcb routing
2026-06-04 Add support for additional pronouns in profile setup and update styles
2026-06-04 web: fix padding on chat
2026-06-05 Enhance support functionality by adding context classification and abuse reporting features. Update user data structure to track support abuse counts and ban statuses. Modify support request handling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
2026-06-07 feat: Implement theme toggle and text streaming functionality
    - Added theme toggle feature to switch between light and dark modes.
    - Implemented theme persistence using localStorage.
    - Enhanced user interface with new styles for light mode.
    - Introduced WebSocket support for streaming text responses from the backend.
    - Updated backend to handle streaming text requests and send responses in chunks.
    - Improved error handling for WebSocket connections.
2026-06-07 start component placing on pcb
2026-06-08 moar pcb
2026-06-08 4layer brain pcb
2026-06-13 finsihed pcb?
2026-06-13 more DRC
2026-06-13 no DRC ERRORS
2026-06-13 no DRC important warnings
2026-06-13 make pcb fit into 100x100mm area
2026-06-13 fix DRC
2026-06-13 sarcasmos logo
2026-06-13 finish pcb fr
2026-06-13 export PCBs
2026-06-14 newBenderCAD
2026-06-15 New bass
2026-06-15 visor w/ pcbs
2026-06-15 fix: visor w/ pcbs
2026-06-15 top, colors and fixes
2026-06-15 groupBase
2026-06-16 motor Hole
2026-06-16 folders
2026-06-16 plans
2026-06-16 unify BOM
2026-06-17 add more components to bom
2026-06-18 remove duplicates
2026-06-19 add prices
2026-06-19 nvm, remove price
2026-06-19 poster carpet
2026-06-20 Protect local secrets from git
2026-06-20 brainCode
2026-06-20 EyeCode
2026-06-20 MouthCode
2026-06-20 stuff done
2026-06-20 images
2026-06-20 Zine
2026-06-20 finish README
2026-06-20 fix use of python3
2026-06-20 Finishing touches
2026-06-20 add AutoAuth mode
2026-06-20 Add popup when no credits are left in api key
2026-06-20 add .env option to enable AutoAuth
2026-06-20 fix Add popup when no credits are left in api key
2026-06-20 floating credit chip to left
2026-06-20 remove comment
2026-06-20 Add BOM
2026-06-20 Why did we build this?
2026-06-23 exports
2026-06-23 fix exports
2026-06-23 move interiorSarcsamos
2026-06-23 animViz
